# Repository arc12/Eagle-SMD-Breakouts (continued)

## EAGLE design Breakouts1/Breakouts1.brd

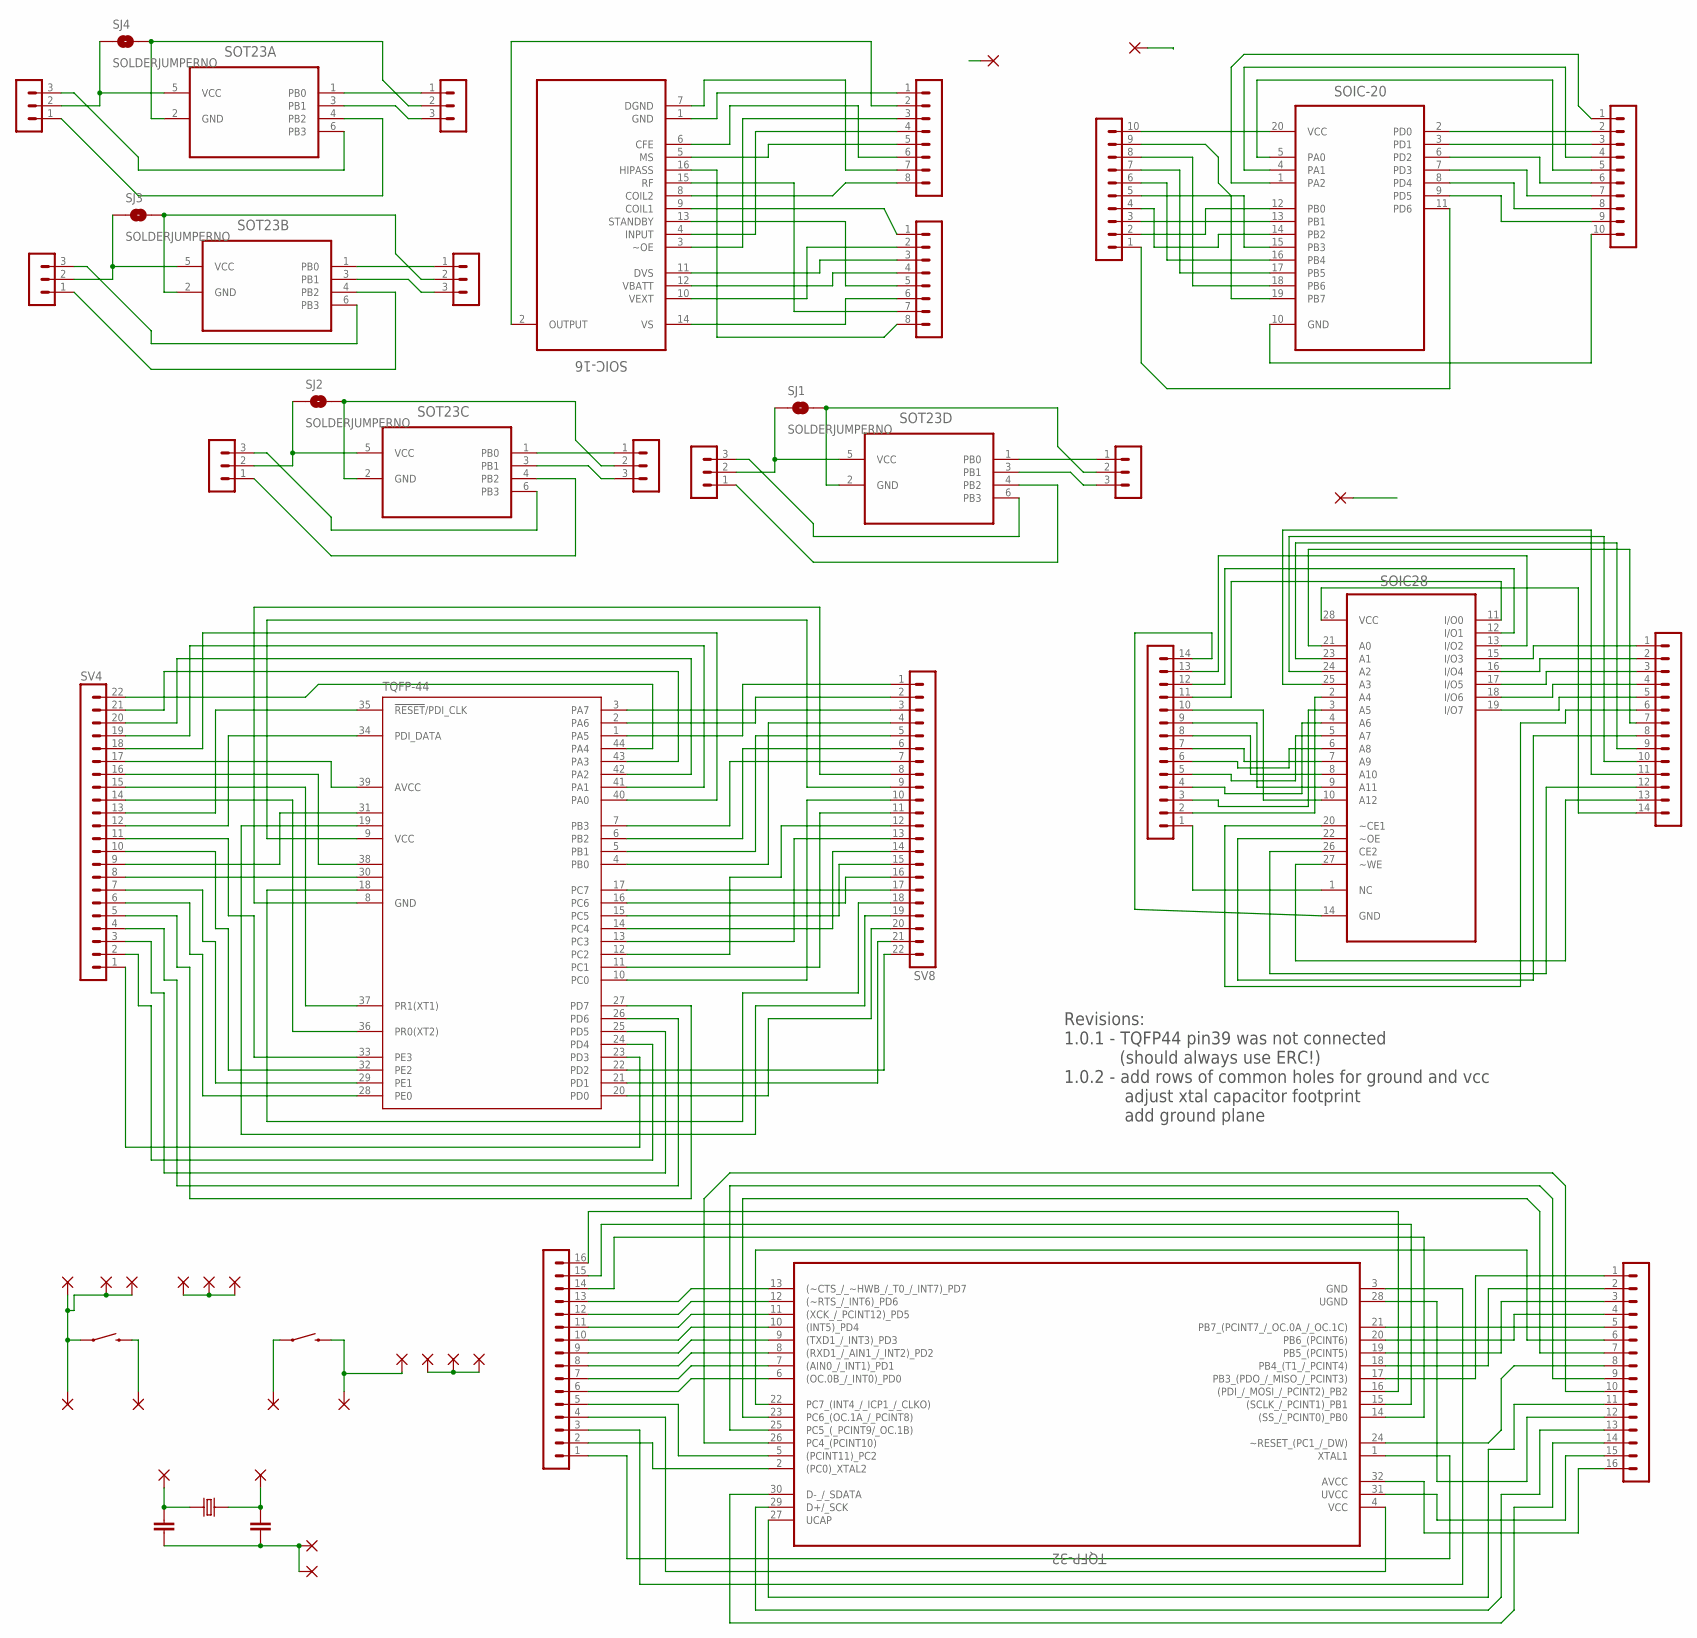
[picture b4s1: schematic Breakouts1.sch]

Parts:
C1, C2: C-EU025-024X044**100NF+22PF; C025-024X044
PAD1, PAD2, PAD3, PAD4, PAD5, PAD6, PAD7, PAD8, PAD9, PAD10, PAD11, PAD12, PAD13, PAD14, PAD15, PAD16, PAD17, PAD18: WIREPAD1,6/0,8; 1,6/0,8
PLANE-SOIC16, PLANE-SOIC20, PLANE-SOIC28: WIREPAD1,6/0,8; 1,6/0,8
S1, S2: SWITCH-MOMENTARY-2PTH; TACTILE-PTH
SJ1, SJ2, SJ3, SJ4: SOLDERJUMPERNO; SJ_2S-NO
SOIC28: CY6264-70SNXC; SOIC127P1193X253-28N
SOIC-16: U2270B-MFPY; SOIC127P600X140-16N
SOIC-20: ATTINY2313A-SU; SOIC127P1032X265-20N
SOT23A, SOT23B, SOT23C, SOT23D: ATTINY10-TSHR; SOT95P280X145-6N
SV1, SV2: MA08-1
SV3, SV7: MA16-1
SV4, SV8: MA22-1
SV5, SV9: MA14-1
SV6, SV17: MA10-1
SV10, SV11, SV12, SV13, SV14, SV15, SV21, SV22: MA03-1
TQFP-32: AT90USB162-16AU; QFP80P900X900X120-32N
TQFP-44: XMEGA16A4A; TQFP44
X1: CRYSTAL-HC49U-V**16MHZ; HC49U-V

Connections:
GND: C1.2, C2.2, PAD2.1, PAD5.1, PAD8.1, PAD9.1, PAD10.1, PAD14.1, S1.1
unnamed: SV8.1, TQFP-44.1 (PA5)
unnamed: SV8.2, TQFP-44.2 (PA6)
unnamed: SV8.3, TQFP-44.3 (PA7)
unnamed: SV8.4, TQFP-44.4 (PB0)
unnamed: SV8.5, TQFP-44.5 (PB1)
unnamed: SV8.6, TQFP-44.6 (PB2)
unnamed: SV8.7, TQFP-44.7 (PB3)
unnamed: SV8.8, TQFP-44.8 (GND)
unnamed: SV8.9, TQFP-44.9 (VCC)
unnamed: SV8.12, TQFP-44.12 (PC2)
unnamed: SV8.11, TQFP-44.11 (PC1)
unnamed: SV8.10, TQFP-44.10 (PC0)
unnamed: SV8.13, TQFP-44.13 (PC3)
unnamed: SV8.14, TQFP-44.14 (PC4)
unnamed: SV8.15, TQFP-44.15 (PC5)
unnamed: SV8.16, TQFP-44.16 (PC6)
unnamed: SV8.17, TQFP-44.17 (PC7)
unnamed: SV8.18, TQFP-44.18 (GND1)
unnamed: SV8.19, TQFP-44.19 (VCC1)
unnamed: SV8.20, TQFP-44.20 (PD0)
unnamed: SV8.21, TQFP-44.21 (PD1)
unnamed: SV8.22, TQFP-44.22 (PD2)
unnamed: SV4.1, TQFP-44.23 (PD3)
unnamed: SV4.2, TQFP-44.24 (PD4)
unnamed: SOIC28.1 (NC), SV9.1
unnamed: SOIC28.2 (A4), SV9.2
unnamed: SOIC28.3 (A5), SV9.3
unnamed: SOIC28.4 (A6), SV9.4
unnamed: SOIC28.5 (A7), SV9.5
unnamed: SOIC28.6 (A8), SV9.6
unnamed: SOIC28.7 (A9), SV9.7
unnamed: SOIC28.8 (A10), SV9.8
unnamed: SV4.3, TQFP-44.25 (PD5)
unnamed: SV4.4, TQFP-44.26 (PD6)
unnamed: SV4.5, TQFP-44.27 (PD7)
unnamed: SV4.6, TQFP-44.28 (PE0)
unnamed: SV4.7, TQFP-44.29 (PE1)
unnamed: SV4.8, TQFP-44.30 (GND2)
unnamed: SV4.9, TQFP-44.31 (VCC2)
unnamed: SV4.10, TQFP-44.32 (PE2)
unnamed: SV4.11, TQFP-44.33 (PE3)
unnamed: SV4.12, TQFP-44.34 (PDI_DATA)
unnamed: SV4.13, TQFP-44.35 (!RESET!/PDI_CLK)
unnamed: SV4.14, TQFP-44.36 (PR0(XT2))
unnamed: SV4.15, TQFP-44.37 (PR1(XT1))
unnamed: SOIC-20.1 (PA2), SV6.1
unnamed: SOIC-20.2 (PD0), SV6.2
unnamed: SOIC-20.3 (PD1), SV6.3
unnamed: SOIC-20.4 (PA1), SV6.4
unnamed: SOIC-20.5 (PA0), SV6.5
unnamed: SOIC-20.6 (PD2), SV6.6
unnamed: SOIC-20.7 (PD3), SV6.7
unnamed: SOIC-20.8 (PD4), SV6.8
unnamed: SOIC-20.9 (PD5), SV6.9
unnamed: SOIC-20.10 (GND), SV6.10
unnamed: SOIC-20.11 (PD6), SV17.1
unnamed: SOIC-20.12 (PB0), SV17.2
unnamed: SOIC-20.13 (PB1), SV17.3
unnamed: SOIC-20.14 (PB2), SV17.4
unnamed: SOIC-20.15 (PB3), SV17.5
unnamed: SOIC-20.16 (PB4), SV17.6
unnamed: SOIC-20.18 (PB6), SV17.8
unnamed: SOIC-20.19 (PB7), SV17.9
unnamed: SOIC-20.20 (VCC), SV17.10
unnamed: SV4.16, TQFP-44.38 (GND3)
unnamed: SV4.17, TQFP-44.39 (AVCC)
unnamed: SV4.18, TQFP-44.40 (PA0)
unnamed: SV4.19, TQFP-44.41 (PA1)
unnamed: SV4.20, TQFP-44.42 (PA2)
unnamed: SV4.21, TQFP-44.43 (PA3)
unnamed: SV4.22, TQFP-44.44 (PA4)
unnamed: SOIC-20.17 (PB5), SV17.7
unnamed: SV7.2, TQFP-32.2 ((PC0)_XTAL2)
unnamed: SV7.1, TQFP-32.1 (XTAL1)
unnamed: SV7.5, TQFP-32.5 ((PCINT11)_PC2)
unnamed: SV7.6, TQFP-32.6 ((OC.0B_/_INT0)_PD0)
unnamed: SV7.7, TQFP-32.7 ((AIN0_/_INT1)_PD1)
unnamed: SV7.8, TQFP-32.8 ((RXD1_/_AIN1_/_INT2)_PD2)
unnamed: SV7.9, TQFP-32.9 ((TXD1_/_INT3)_PD3)
unnamed: SV7.10, TQFP-32.10 ((INT5)_PD4)
unnamed: SV7.11, TQFP-32.11 ((XCK_/_PCINT12)_PD5)
unnamed: SV7.12, TQFP-32.12 ((~RTS_/_INT6)_PD6)
unnamed: SV7.13, TQFP-32.13 ((~CTS_/_~HWB_/_T0_/_INT7)_PD7)
unnamed: SV7.4, TQFP-32.4 (VCC)
unnamed: SV7.3, TQFP-32.3 (GND)
unnamed: SV7.16, TQFP-32.16 ((PDI_/_MOSI_/_PCINT2)_PB2)
unnamed: SV7.15, TQFP-32.15 ((SCLK_/_PCINT1)_PB1)
unnamed: SV7.14, TQFP-32.14 ((SS_/_PCINT0)_PB0)
unnamed: SV3.1, TQFP-32.17 (PB3_(PDO_/_MISO_/_PCINT3))
unnamed: SV3.2, TQFP-32.18 (PB4_(T1_/_PCINT4))
unnamed: SV3.3, TQFP-32.19 (PB5_(PCINT5))
unnamed: SV3.4, TQFP-32.20 (PB6_(PCINT6))
unnamed: SV3.5, TQFP-32.21 (PB7_(PCINT7_/_OC.0A_/_OC.1C))
unnamed: SV3.6, TQFP-32.22 (PC7_(INT4_/_ICP1_/_CLKO))
unnamed: SV3.7, TQFP-32.23 (PC6_(OC.1A_/_PCINT8))
unnamed: SV3.8, TQFP-32.24 (~RESET_(PC1_/_DW))
unnamed: SV3.9, TQFP-32.25 (PC5_(_PCINT9/_OC.1B))
unnamed: SV3.10, TQFP-32.26 (PC4_(PCINT10))
unnamed: SV3.11, TQFP-32.27 (UCAP)
unnamed: SV3.12, TQFP-32.28 (UGND)
unnamed: SV3.13, TQFP-32.29 (D+/_SCK)
unnamed: SV3.14, TQFP-32.30 (D-_/_SDATA)
unnamed: SV3.15, TQFP-32.31 (UVCC)
unnamed: SV3.16, TQFP-32.32 (AVCC)
unnamed: SOIC-16.1 (GND), SV1.1
unnamed: SOIC-16.2 (OUTPUT), SV1.2
unnamed: SOIC-16.3 (~OE), SV1.3
unnamed: SOIC-16.4 (INPUT), SV1.4
unnamed: SOIC-16.5 (MS), SV1.5
unnamed: SOIC-16.6 (CFE), SV1.6
unnamed: SOIC-16.7 (DGND), SV1.7
unnamed: SOIC-16.8 (COIL2), SV1.8
unnamed: SOIC-16.9 (COIL1), SV2.1
unnamed: SOIC-16.10 (VEXT), SV2.2
unnamed: SOIC-16.11 (DVS), SV2.3
unnamed: SOIC-16.12 (VBATT), SV2.4
unnamed: SOIC-16.13 (STANDBY), SV2.5
unnamed: SOIC-16.14 (VS), SV2.6
unnamed: SOIC-16.15 (RF), SV2.7
unnamed: SOIC-16.16 (HIPASS), SV2.8
unnamed: SOT23C.1 (PB0), SV22.1
unnamed: SJ2.2, SOT23C.2 (GND), SV22.2
unnamed: SOT23C.3 (PB1), SV22.3
unnamed: SOT23C.4 (PB2), SV21.1
unnamed: SJ2.1, SOT23C.5 (VCC), SV21.2
unnamed: SOT23C.6 (PB3), SV21.3
unnamed: SOIC28.9 (A11), SV9.9
unnamed: SOIC28.10 (A12), SV9.10
unnamed: SOIC28.11 (I/O0), SV9.11
unnamed: SOIC28.12 (I/O1), SV9.12
unnamed: SOIC28.13 (I/O2), SV9.13
unnamed: SOIC28.14 (GND), SV9.14
unnamed: SOIC28.15 (I/O3), SV5.1
unnamed: SOIC28.16 (I/O4), SV5.2
unnamed: SOIC28.17 (I/O5), SV5.3
unnamed: SOIC28.18 (I/O6), SV5.4
unnamed: SOIC28.19 (I/O7), SV5.5
unnamed: SOIC28.20 (~CE1), SV5.6
unnamed: SOIC28.21 (A0), SV5.7
unnamed: SOIC28.22 (~OE), SV5.8
unnamed: SOIC28.23 (A1), SV5.9
unnamed: SOIC28.24 (A2), SV5.10
unnamed: SOIC28.25 (A3), SV5.11
unnamed: SOIC28.26 (CE2), SV5.12
unnamed: SOIC28.27 (~WE), SV5.13
unnamed: SOIC28.28 (VCC), SV5.14
unnamed: SOT23B.1 (PB0), SV11.1
unnamed: SJ3.2, SOT23B.2 (GND), SV11.2
unnamed: SOT23B.3 (PB1), SV11.3
unnamed: SOT23B.4 (PB2), SV10.1
unnamed: SJ3.1, SOT23B.5 (VCC), SV10.2
unnamed: SOT23B.6 (PB3), SV10.3
unnamed: SOT23D.1 (PB0), SV13.1
unnamed: SJ1.2, SOT23D.2 (GND), SV13.2
unnamed: SOT23D.3 (PB1), SV13.3
unnamed: SOT23D.4 (PB2), SV12.1
unnamed: SJ1.1, SOT23D.5 (VCC), SV12.2
unnamed: SOT23D.6 (PB3), SV12.3
unnamed: SOT23A.1 (PB0), SV15.1
unnamed: SJ4.2, SOT23A.2 (GND), SV15.2
unnamed: SOT23A.3 (PB1), SV15.3
unnamed: SOT23A.4 (PB2), SV14.1
unnamed: SJ4.1, SOT23A.5 (VCC), SV14.2
unnamed: SOT23A.6 (PB3), SV14.3
unnamed: PAD1.1, S1.3 (2)
unnamed: PAD4.1, S2.1
unnamed: C2.1, PAD6.1, X1.1
unnamed: C1.1, PAD7.1, X1.2
unnamed: PAD16.1, PAD17.1, PAD18.1
unnamed: PAD11.1, PAD12.1, PAD13.1
PLANE-SOIC16: PLANE-SOIC16.1
PLANE-SOIC20: PLANE-SOIC20.1
PLANE-SOIC28: PLANE-SOIC28.1
PLANE-TQFP32: PAD3.1, PAD15.1, S2.3 (2)

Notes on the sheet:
Revisions: 1.0.1 - TQFP44 pin39 was not connected (should always use ERC!) 1.0.2 - add rows of common holes for ground and vcc adjust xtal capacitor footprint add ground plane

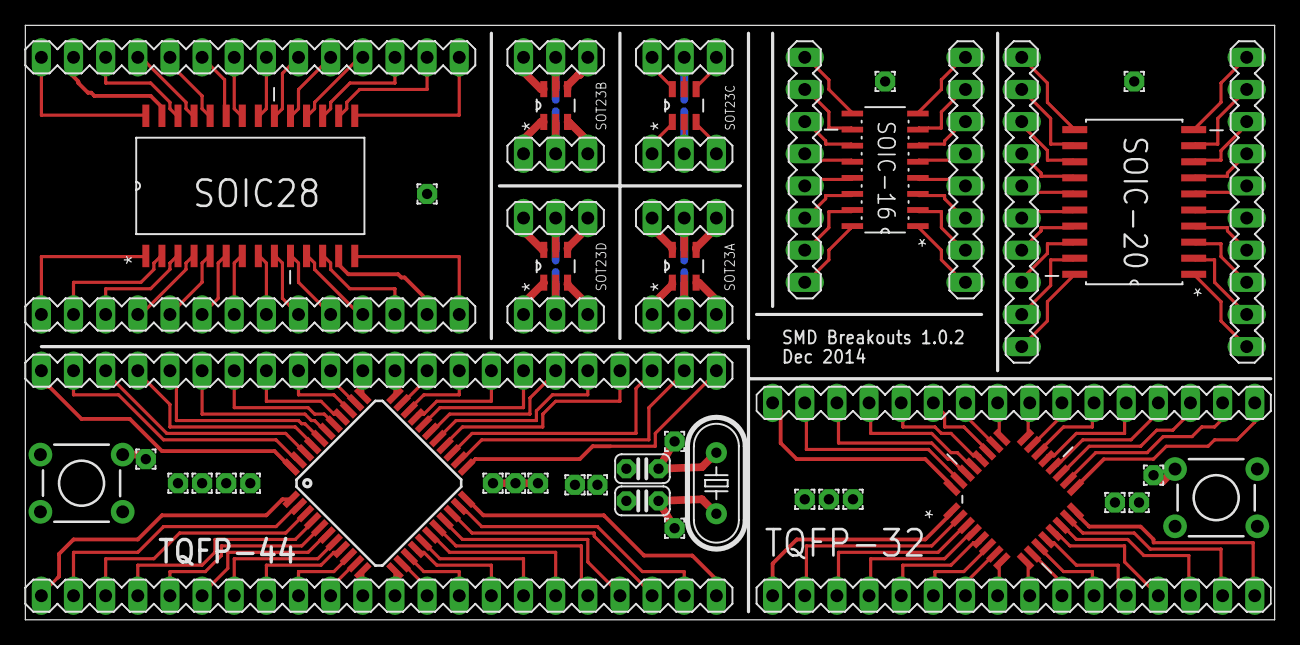
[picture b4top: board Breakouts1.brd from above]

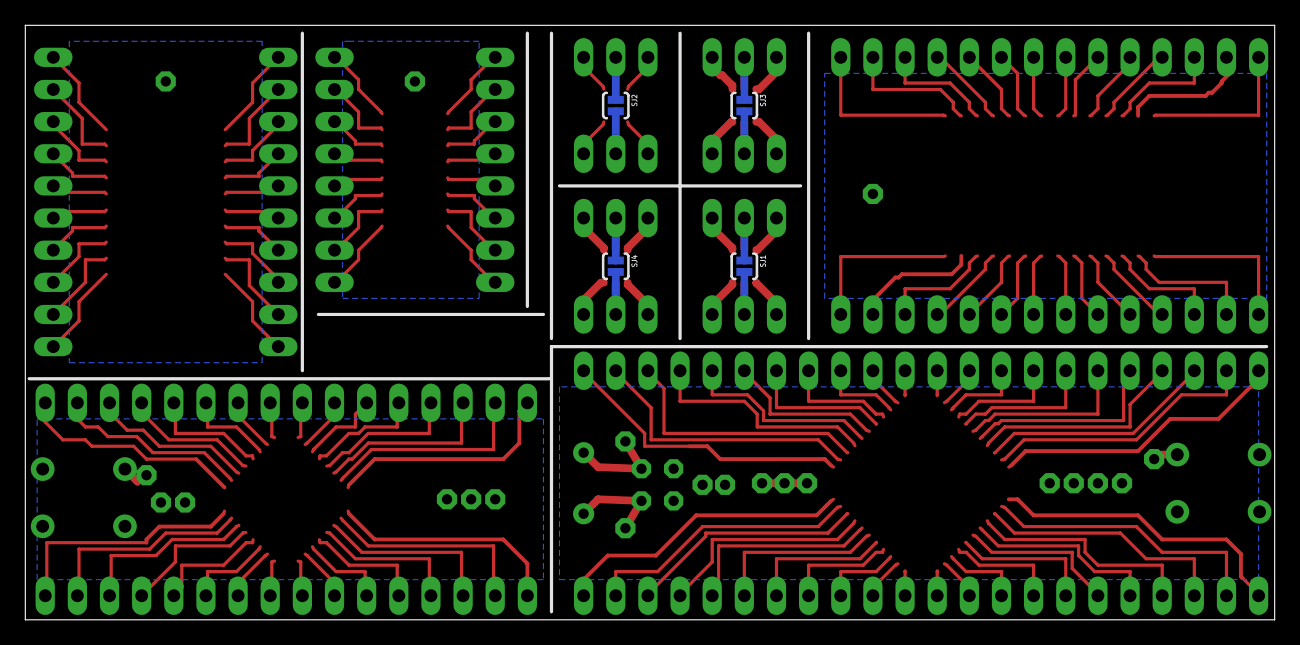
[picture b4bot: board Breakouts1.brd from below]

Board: 2 copper layers, 98.7 x 47.0 mm, 57 parts (4 on the bottom side), 172 nets.

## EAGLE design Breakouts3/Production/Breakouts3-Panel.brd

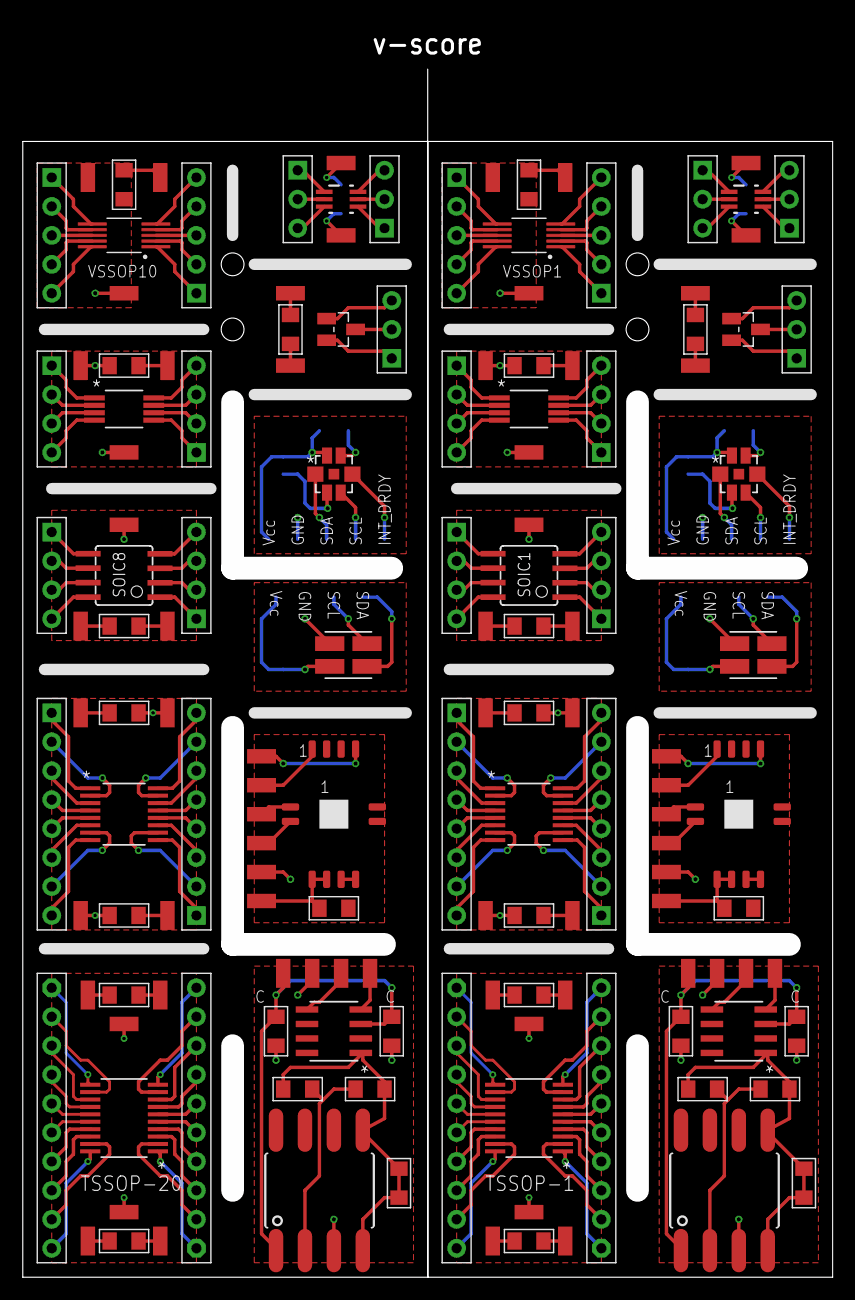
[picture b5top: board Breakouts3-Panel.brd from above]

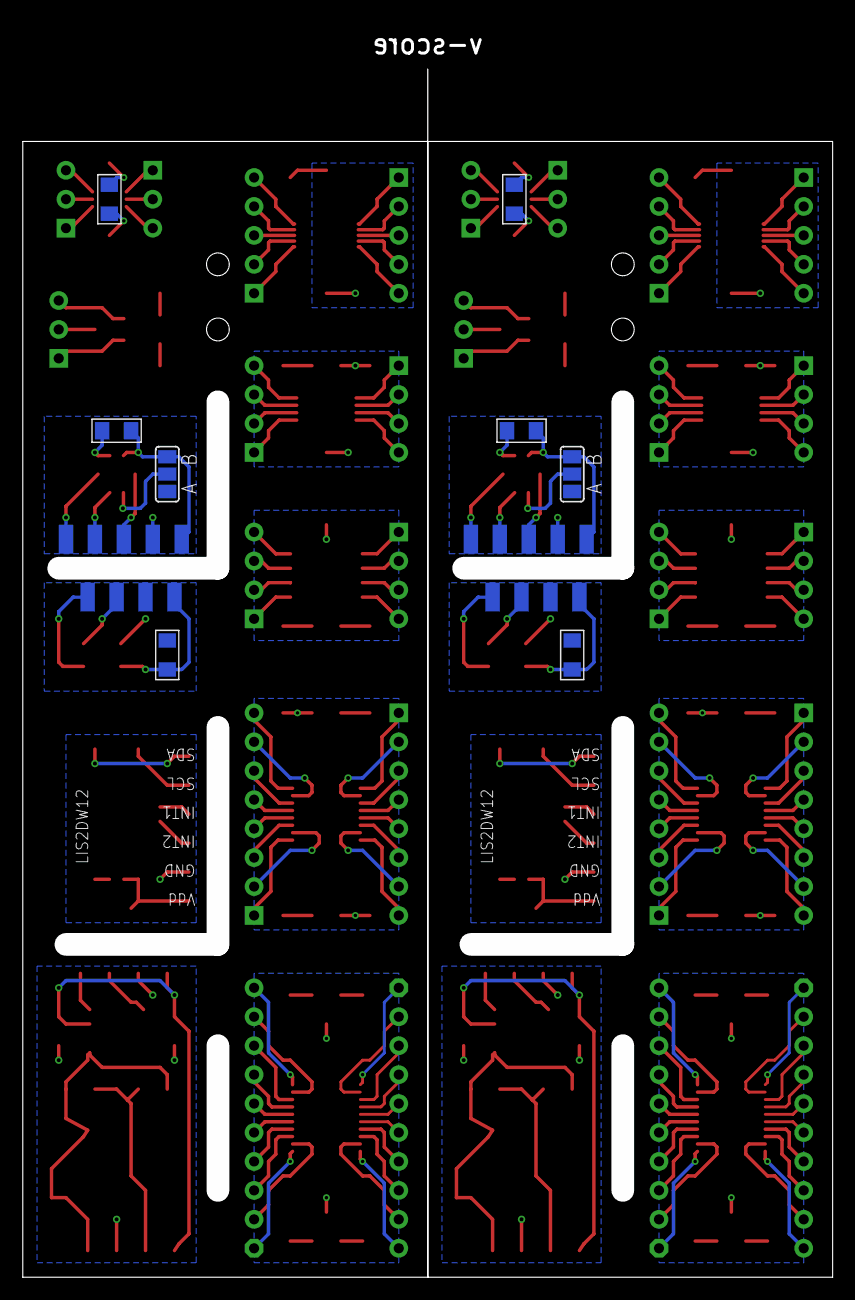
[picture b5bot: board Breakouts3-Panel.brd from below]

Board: 2 copper layers, 69.1 x 108.1 mm, 176 parts (26 on the bottom side), 222 nets.

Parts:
C1, C2, C3, C4, C5, C6, C7, C8, C9, C10, C11, C12, C13, C14, C15, C16, C17, C18, C19, C20, C21, C22, C23, C24, C25, C26, C27, C28: 1206
CLGA-1, CLGA-7: LPS28DFW; CCLGA7_LPS28DFW_LARGE
J1, J2, J16, J17: 10P-2.54
J3, J4, J18, J19: 4P-1.27-SMD
J5, J6, J20, J21: 8P-2.54
J7, J8, J13, J22, J23, J28: 3P-2.54
J9, J10, J11, J12, J24, J25, J26, J27: 4P-65/35MIL
J14, J15, J29, J30: 5P-2.54
MSOP1, MSOP8: MCP4532-104E/MSMSOP8_MC_MCH-M; MSOP8_MC_MCH-M
PAD1, PAD2, PAD3, PAD4, PAD5, PAD6, PAD7, PAD8, PAD9, PAD10, PAD11, PAD12, PAD13, PAD14, PAD15, PAD16, PAD17, PAD18, PAD19, PAD20, PAD21, PAD22, PAD23, PAD24, PAD25, PAD26, PAD27, PAD28, PAD29, PAD30, PAD31, PAD32, PAD33, PAD34, PAD35, PAD36, PAD37, PAD38, PAD39, PAD40, PAD41, PAD42, PAD43, PAD44, PAD45, PAD46, PAD47, PAD48, PAD49, PAD50, PAD51, PAD52, PAD53, PAD54, PAD55, PAD56, PAD57, PAD58, PAD59, PAD60, PAD61, PAD62, PAD63, PAD64, PAD65, PAD66, PAD67, PAD68, PAD69, PAD70, PAD71, PAD72, PAD73, PAD74, PAD75, PAD76, PAD77, PAD78, PAD79, PAD80, PAD81, PAD82, PAD83, PAD84: WIREPADSMD1,27-254; SMD1,27-2,54
Q1, Q2: SOT23_LONG
R1, R2, R3, R4, R5, R6: 1206
SJ1, SJ2: SJ_2
SOIC1, SOIC8: TINY10S; SOIC8
TSSOP-1, TSSOP-20: SN74ACT245PWRPW20-M; PW20-M
TSSOP-2, TSSOP-16: SC18IM704PWJSOT403-1_NXP-M; SOT403-1_NXP-M
U1, U5: MS5837; MS5837-02BA01_LARGE
U2, U6: TMP117AIDRVRLARGE; DRV0006B-LARGE
U3, U7: OPT101; DTL0008A_LARGE
U4, U8: MCP3426; SOIC8-N_MC_MCH
U$1, U$2, U$3, U$4: HEADER-2P; 2P-1.27-SMD
VSSOP1, VSSOP10: FDC1004DGSR; SOP50P490X110-10N

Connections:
AGND: PAD15.1, PAD16.1
AGND1: PAD57.1, PAD58.1
B1: J3.1, PAD3.1
B4: J3.4, PAD6.1
B6: C1.1, J4.1, J4.2, PAD1.1, U$1.2
B7: C15.2, J19.3, J19.4, PAD44.1
B9: C1.2, J4.3, J4.4, PAD2.1
B10: J18.1, PAD45.1
B11: PAD4.1, U$2.1
B12: PAD5.1, U$2.2
B14: C15.1, J19.1, J19.2, PAD43.1, U$3.2
B15: J18.4, PAD48.1
B16: PAD46.1, U$4.1
B17: PAD47.1, U$4.2
CGND: C2.1, PAD7.1, U1.1
CGND1: C16.1, PAD49.1, U5.1
D1: J8.1, U2.1
D2: J8.2, U2.2
D3: J8.3, U2.3
D4: J7.1, U2.4
D5: J7.2, U2.5
D6: J7.3, U2.6
D7: J22.2, U6.5
D8: J22.3, U6.6
D9: J23.1, U6.1
D10: J23.3, U6.3
D11: J22.1, U6.4
D12: J23.2, U6.2
EGND: C5.2, C9.2, PAD24.1, U3.3, U3.8, U4.2, U4.6, U4.7, U4.8
EGND1: C19.2, C23.2, PAD66.1, U7.3, U7.8, U8.2, U8.6, U8.7, U8.8
ESCL: PAD25.1, U4.5
ESCL1: PAD67.1, U8.5
ESDA: PAD26.1, U4.4
ESDA1: PAD68.1, U8.4
EV+: C5.1, C9.1, PAD23.1, U3.1, U4.3
EV+1: C19.1, C23.1, PAD65.1, U7.1, U8.3
FGND: C7.1, C8.2, PAD20.1, PAD21.1
FGND1: C21.1, C22.2, PAD62.1, PAD63.1
G1: J10.1, SOIC8.1
G2: J10.2, SOIC8.2
G3: J10.3, SOIC8.3
G4: J10.4, SOIC8.4
G5: J9.1, SOIC8.5
G6: J9.2, SOIC8.6
G7: J9.3, SOIC8.7
G8: J9.4, SOIC8.8
G9: J24.4, SOIC1.8
G10: J25.4, SOIC1.4
G11: J25.1, SOIC1.1
G12: J25.3, SOIC1.3
G13: J25.2, SOIC1.2
G14: J24.3, SOIC1.7
G15: J24.2, SOIC1.6
G16: J24.1, SOIC1.5
GGND: C11.1, PAD27.1, PAD29.1
GGND1: C25.1, PAD69.1, PAD71.1
HGND: C12.1, PAD31.1, PAD32.1
HGND1: C26.1, PAD73.1, PAD74.1
I1: CLGA-7.1, PAD34.1
I2: CLGA-7.2, SJ1.2
I3: CLGA-7.3, PAD35.1
I4: CLGA-7.4, PAD36.1
I5: CLGA-1.1, PAD75.1
I6: C14.2, CLGA-7.6, PAD38.1, SJ1.3
I7: CLGA-1.2, SJ2.2
I8: CLGA-1.3, PAD76.1
I9: CLGA-1.4, PAD77.1
I10: C27.2, CLGA-1.6, PAD79.1, SJ2.3
IGND: C14.1, CLGA-7.5, PAD37.1, SJ1.1
IGND1: C27.1, CLGA-1.5, PAD78.1, SJ2.1
J1: J14.1, VSSOP10.1
J2: J14.2, VSSOP10.2
J3: J14.3, VSSOP10.3
J4: J14.4, VSSOP10.4
J5: J14.5, VSSOP10.5
J6: J15.1, VSSOP10.6
J7: J15.2, VSSOP10.7
J8: J15.3, VSSOP10.8
J9: J15.4, VSSOP10.9
J10: J15.5, VSSOP10.10
J11: J30.1, VSSOP1.6
J12: J30.2, VSSOP1.7
J13: J30.3, VSSOP1.8
J14: J30.4, VSSOP1.9
J15: J30.5, VSSOP1.10
J16: J29.5, VSSOP1.5
J17: J29.4, VSSOP1.4
J18: J29.3, VSSOP1.3
J19: J29.2, VSSOP1.2
J20: J29.1, VSSOP1.1
JGND: C13.1, PAD41.1, PAD42.1
JGND1: C28.1, PAD83.1, PAD84.1
unnamed: J1.1, TSSOP-20.1
unnamed: C2.2, PAD8.1, U1.2
unnamed: PAD9.1, U1.4
unnamed: PAD10.1, U1.3
unnamed: J1.2, TSSOP-20.2
unnamed: J1.3, TSSOP-20.3
unnamed: J1.4, TSSOP-20.4
unnamed: J1.5, TSSOP-20.5
unnamed: J1.6, TSSOP-20.6
unnamed: J1.7, TSSOP-20.7
unnamed: J1.8, TSSOP-20.8
unnamed: J1.9, TSSOP-20.9
unnamed: J1.10, TSSOP-20.10
unnamed: J2.10, TSSOP-20.20
unnamed: J2.9, TSSOP-20.19
unnamed: J2.8, TSSOP-20.18
unnamed: J2.7, TSSOP-20.17
unnamed: J2.6, TSSOP-20.16
unnamed: J2.5, TSSOP-20.15
unnamed: J2.4, TSSOP-20.14
unnamed: J2.3, TSSOP-20.13
unnamed: J2.2, TSSOP-20.12
unnamed: J2.1, TSSOP-20.11
unnamed: C3.1, PAD11.1
unnamed: C3.2, PAD13.1
unnamed: C4.1, PAD12.1
unnamed: C4.2, PAD14.1
unnamed: C6.1, PAD17.1
unnamed: C6.2, PAD18.1
unnamed: C7.2, PAD22.1
unnamed: PAD33.1, R3.1
unnamed: C10.1, R1.1, R2.1, R2.2, U3.4, U3.5, U4.1
unnamed: C8.1, PAD19.1
unnamed: J6.1, TSSOP-16.1
unnamed: J6.2, TSSOP-16.2
unnamed: J6.3, TSSOP-16.3
unnamed: J6.4, TSSOP-16.4
unnamed: J6.5, TSSOP-16.5
unnamed: J6.6, TSSOP-16.6
unnamed: J6.7, TSSOP-16.7
unnamed: J6.8, TSSOP-16.8
unnamed: J5.8, TSSOP-16.16
unnamed: J5.7, TSSOP-16.15
unnamed: J5.6, TSSOP-16.14
unnamed: J5.5, TSSOP-16.13
unnamed: J5.4, TSSOP-16.12
unnamed: J5.3, TSSOP-16.11
unnamed: J5.2, TSSOP-16.10
unnamed: J5.1, TSSOP-16.9
unnamed: C10.2, R1.2, U3.2
unnamed: C11.2, PAD28.1
unnamed: J12.1, MSOP8.1
unnamed: J12.2, MSOP8.2
unnamed: J12.3, MSOP8.3
unnamed: J12.4, MSOP8.4
unnamed: J11.4, MSOP8.8
unnamed: J11.3, MSOP8.7
unnamed: J11.2, MSOP8.6
unnamed: J11.1, MSOP8.5
unnamed: PAD39.1, R3.2
unnamed: C12.2, PAD30.1
unnamed: J13.3, Q1.1
unnamed: J13.2, Q1.3
unnamed: J13.1, Q1.2
unnamed: C16.2, PAD50.1, U5.2
unnamed: C13.2, PAD40.1
unnamed: PAD51.1, U5.4
unnamed: PAD52.1, U5.3
unnamed: J16.1, TSSOP-1.1
unnamed: J16.2, TSSOP-1.2
unnamed: J16.3, TSSOP-1.3
unnamed: J16.4, TSSOP-1.4
unnamed: J16.5, TSSOP-1.5
unnamed: J16.6, TSSOP-1.6
unnamed: J16.7, TSSOP-1.7
unnamed: J16.8, TSSOP-1.8
unnamed: J16.9, TSSOP-1.9
unnamed: J16.10, TSSOP-1.10
unnamed: J17.10, TSSOP-1.20
unnamed: J17.9, TSSOP-1.19
unnamed: J17.8, TSSOP-1.18
unnamed: J17.7, TSSOP-1.17
unnamed: J17.6, TSSOP-1.16
unnamed: J17.5, TSSOP-1.15
unnamed: J17.4, TSSOP-1.14
unnamed: J17.3, TSSOP-1.13
unnamed: J17.2, TSSOP-1.12
unnamed: J17.1, TSSOP-1.11
unnamed: C17.1, PAD53.1
unnamed: C17.2, PAD55.1
unnamed: C18.1, PAD54.1
unnamed: C18.2, PAD56.1
unnamed: C20.1, PAD59.1
unnamed: C20.2, PAD60.1
unnamed: C21.2, PAD64.1
unnamed: C22.1, PAD61.1
unnamed: J21.1, TSSOP-2.1
unnamed: J21.2, TSSOP-2.2
unnamed: J21.3, TSSOP-2.3
unnamed: J21.4, TSSOP-2.4
unnamed: J21.5, TSSOP-2.5
unnamed: J21.6, TSSOP-2.6
unnamed: J21.7, TSSOP-2.7
unnamed: J21.8, TSSOP-2.8
unnamed: J20.8, TSSOP-2.16
unnamed: J20.7, TSSOP-2.15
unnamed: J20.6, TSSOP-2.14
unnamed: J20.5, TSSOP-2.13
unnamed: J20.4, TSSOP-2.12
unnamed: J20.3, TSSOP-2.11
unnamed: J20.2, TSSOP-2.10
unnamed: J20.1, TSSOP-2.9
unnamed: C24.1, R4.1, R5.1, R5.2, U7.4, U7.5, U8.1
unnamed: C24.2, R4.2, U7.2
unnamed: C25.2, PAD70.1
unnamed: J27.1, MSOP1.1
unnamed: J27.2, MSOP1.2
unnamed: J27.3, MSOP1.3
unnamed: J27.4, MSOP1.4
unnamed: J26.4, MSOP1.8
unnamed: J26.3, MSOP1.7
unnamed: J26.2, MSOP1.6
unnamed: J26.1, MSOP1.5
unnamed: C26.2, PAD72.1
unnamed: PAD80.1, R6.1
unnamed: PAD81.1, R6.2
unnamed: J28.1, Q2.2
unnamed: J28.3, Q2.1
unnamed: J28.2, Q2.3
unnamed: C28.2, PAD82.1

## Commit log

2025-07-03 initial commit - older stuff + new Breakouts3
2025-07-03 v1.0 sent to seeed
